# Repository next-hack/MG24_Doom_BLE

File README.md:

## MG24 Doom BLE
 Doom port to Silicon Labs' EFR32xG24 and MGM240x series microcontrollers and modules, with BLE multiplayer support.
 Coded by Nicola Wrachien.

The code is based on doomhack's GBA Doom Port (https://github.com/doomhack/GBADoom) with some Kippykip's additions, using the sources published on 2020. Thousands of changes have been made to fit to 256 kB of RAM, restore missing features, and enable multiplayer.

**Warning!** After you import the project on Simplicity Studio, you must "force project generation", so that the Gecko SDK files are copied on it. This is to comply with Silabs' licensing system. See "Building, developing, etc." below.

** News:**

**26/09/2024 Update! We have added support for The Gamepad, an open source gaming console based on the Arduino Nano Matter Board.
Please see https://next-hack.com/index.php/2024/09/21/the-gamepad-an-open-source-diy-handheld-gaming-console/ for more information about build information!
**

**12/03/2024 Update! Now peak 35 fps can be achieved also on 320 x 240 resolution thanks to partial screen refresh!**

**Features**

- Supports 320x200 and 320x240 resolution (the resolution can be changed at compile time)
- All the features of the original Doom are implemented:
  - full detail rendering, with Z-depth lighting.
  - 8-channel sound at 11025 Hz (samples with higher sample-rate are downsampled to 11025 Hz), mixed to 2 stereo channels.
  - Music with OPL2 emulation.
  - Monster behavior and sound propagation implemented.
  - Screen melt effect.
 - Extremely fast. Run almost always above 30 fps at 320x240, and even more at 320x200.
- Single player with save games and cheats support.
- Multiplayer features:
  - Each device can act as server or client.
  - Up to 4 players per game (server + 3 clients).
  - Game/player name can be edited using the menu.
  - Server can kick players in the lobby menu.
  - Clients can choose from up to 4 hosts.
  - Deathmatch or cooperative
  - Monster on/off.
  - Item respawn on/off
  - Time and frag limits.
  - Multiplayer over BLE.
  - Frame rate shown in the bottom-left corner (can be disabled with a compiler directive).
 - Additional features (with respect to vanilla Doom)
   - Player's weapon also is subjected to ambient light (as in PrBoom).
   - Background Doom title image becomes darker when Menus are turned on, to improve readability.
   - During networking games, kills messages are shown.
  - Tested with:
  - Shareware DOOM1.WAD.
  - Full Commercial DOOM.WAD
  - Partial Doom1.WAD v1.9 built-in demo support. Must be enabled by compiler directive.

**What's missing?**
- Only partial demo playback.
- Savegames do not store the whole status (might be implemented later), but only the current level and inventory.
- Need to be seriously debugged and cleaned up.

**Known issues**
- Multiplayer might be unstable in very crowded RF environments, i.e. joining might be difficult and 4-player game sometimes might be slow (from our tests, 3 player game is always fast, going at 30 fps).
- The display controller is driven via SPI and there is no with no vertical sync, so you can spot some artifacts due to sending new frame data, while the display is still refreshing the old frame.
- Only GSDK 4.3.2 is supported for now, with 10.2.1 GCC toolchain.

## Controls:
**Strafe:** alt + Left-Right
**Automap:** use + change weapon
**Menu:** alt + use
**Run** use + up-down

## Hardware:
In the "hardware" subdirectory you will find the project for the SparkFun Thing Plus Matter MGM240P board (SparkDoom subdir) and the WSTK adapter board .

## Content of this repository:
- MCUDoomWadUtil: source of the WAD converter (Code::Blocks project). Note that "mcudoom_0_4.wad" must be put in the same directory as the executable.
- DoomMG24BLE: the actual Doom port (Simplicity Studio 5.5 Project). **note!!!**: after you import the project with Simplicity Studio 5.5 project, you **must** "force generate" the project, so that the gecko sdk directory is recreated. This is because Silabs' GSDK has a different licensing, which requires you do download it from Simplicity Studio and accept the MSLA license.  Although you can download it from [Silicon Labs' github repo](https://github.com/SiliconLabs/gecko_sdk), using Simplicity Studio is strongly recommended, as only only the required files will be added.
- hardware: schematics.

## Building, developing, etc:
See https://next-hack.com/index.php/2023/12/10/multiplayer-doom-on-the-sparkfun-thing-plus-matter-board/
See also: https://next-hack.com/index.php/2024/09/21/the-gamepad-an-open-source-diy-handheld-gaming-console/

## License:
- Hardware: [Solderpad Hardware License version 2.1](https://solderpad.org/licenses/SHL-2.1)
- MCUDoomWadUtil: [GPLv2](https://www.gnu.org/licenses/old-licenses/gpl-2.0.en.html#SEC1)
- DoomMG24BLE
	- Original Doom code, modifications and its additions: GPLv2 or at your option later, as per original Doom/PrBoom sources.
	- [Marco Paland's printf](https://github.com/mpaland/printf): MIT License
	- Silicon Labs' GSDK (**note!** No GSDK files are provided due to its MSLA license, they must be downloaded from Simplicity Studio and restored to the project by forcing project generation): Silicon Lab's MSLA.
	- [Font8x8 By Daniel Hepper](https://github.com/dhepper/font8x8): Public Domain

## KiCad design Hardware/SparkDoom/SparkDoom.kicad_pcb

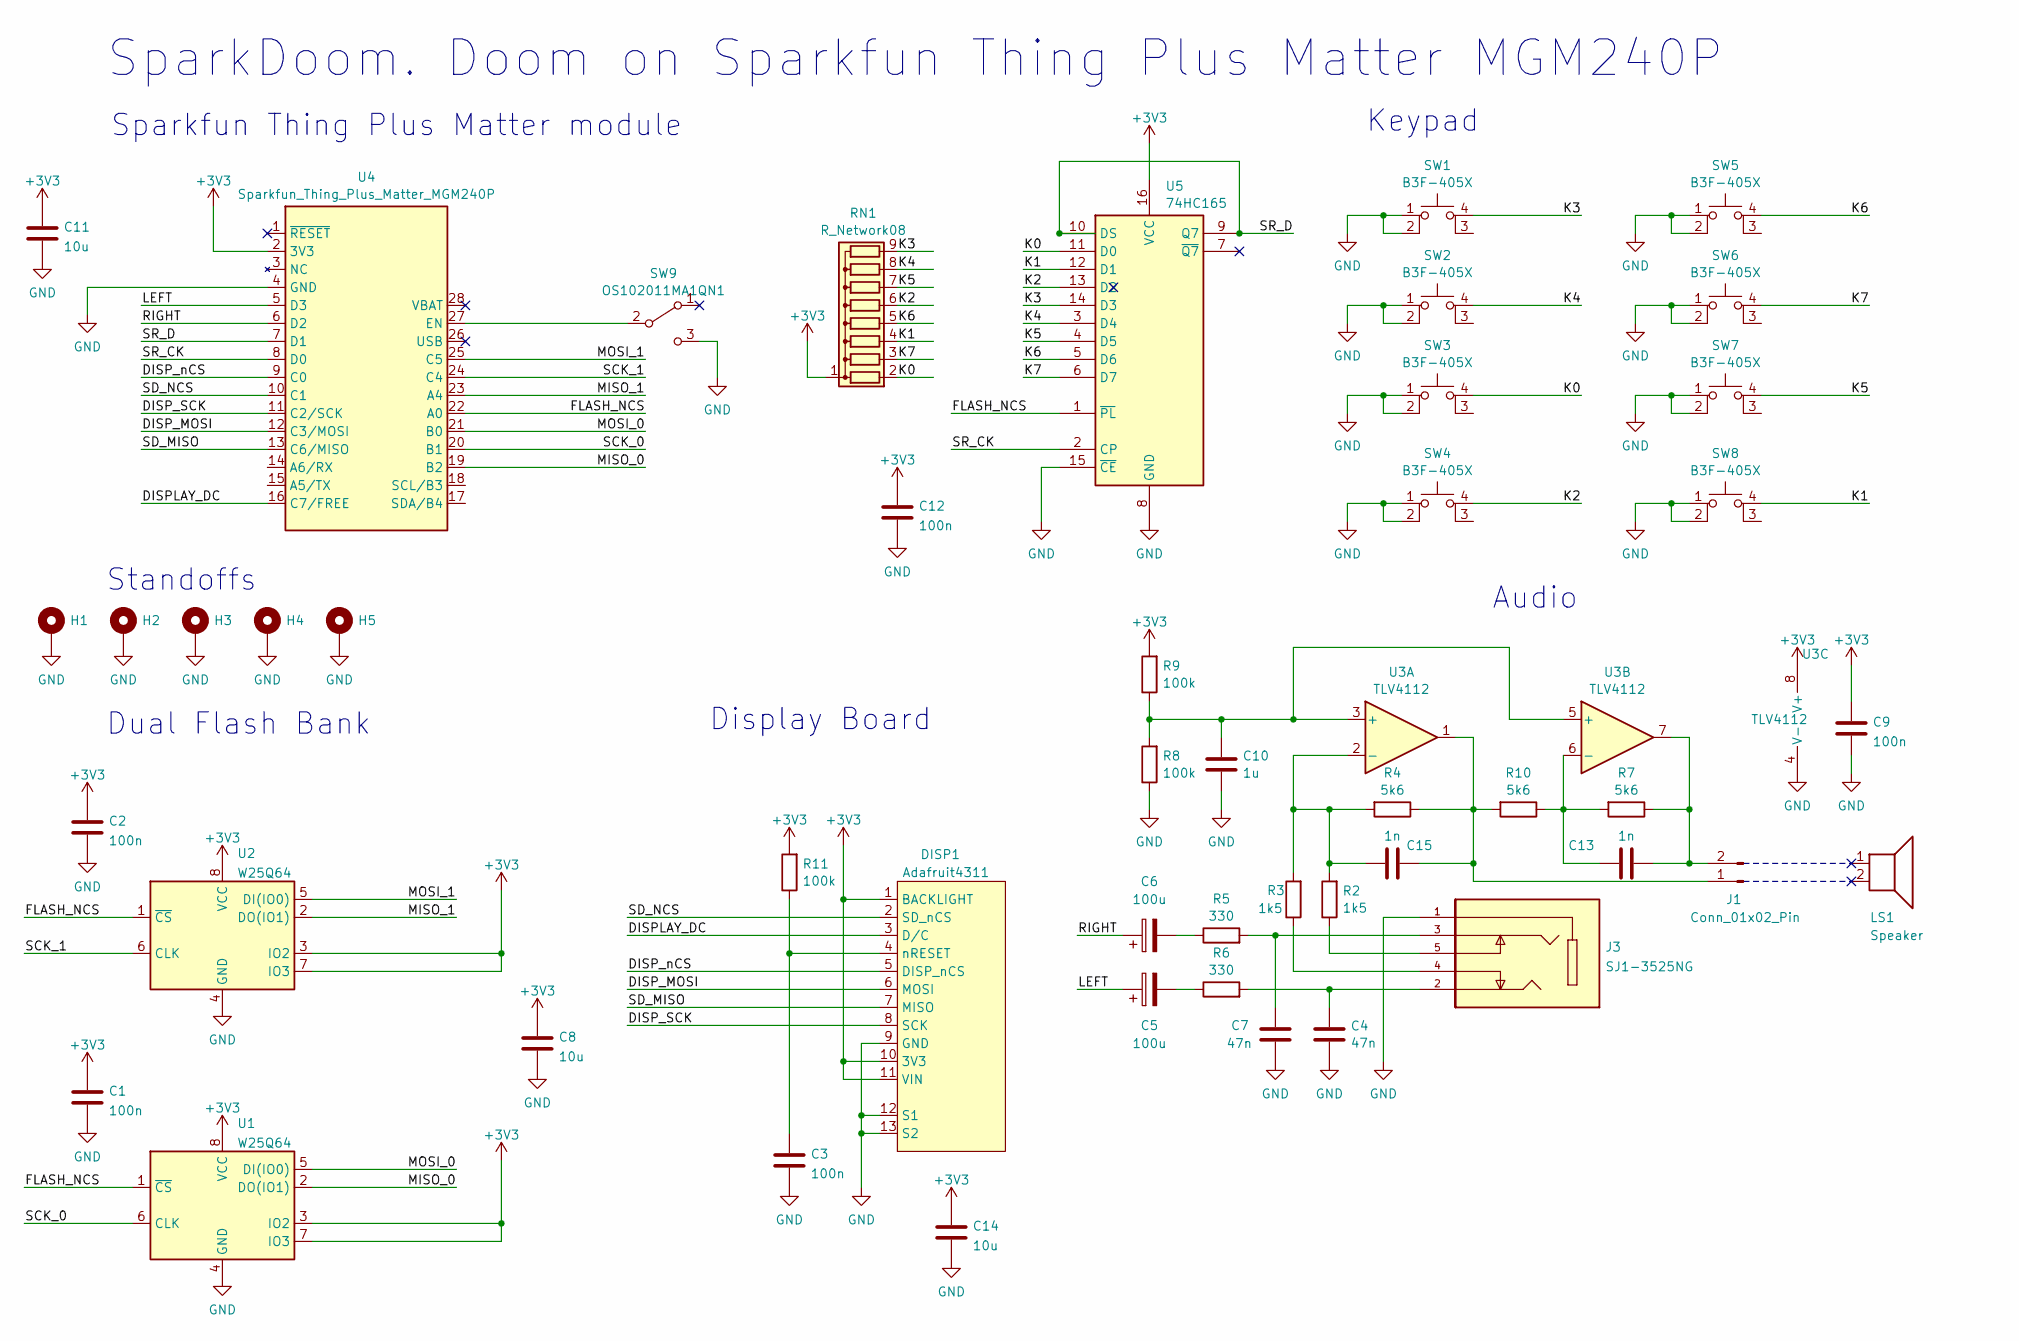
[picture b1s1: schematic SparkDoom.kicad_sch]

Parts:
C1, C2, C3, C9, C12: 100n; C_Disc_D3.8mm_W2.6mm_P2.50mm
C4, C7: 47n; C_Rect_L7.2mm_W2.5mm_P5.00mm_H6.5mm
C5, C6: 100u; CP_Radial_D6.3mm_P2.50mm
C8, C11, C14: 10u; C_Disc_D5.1mm_W3.2mm_P5.00mm
C10: 1u; C_Disc_D5.1mm_W3.2mm_P5.00mm
C13, C15: 1n; C_Disc_D3.8mm_W2.6mm_P2.50mm
DISP1: Adafruit4311
H1, H2, H3, H4, H5: MountingHole_Pad; MountingHole_2.7mm_M2.5_Pad
J1: Conn_01x02_Pin; PinHeader_1x02_P2.54mm_Horizontal
J3: SJ1-3525NG; CUI_SJ1-3525NG; PARTREV 1.01
LS1: Speaker; OWS-1330TA-8
R2, R3: 1k5; R_Axial_DIN0207_L6.3mm_D2.5mm_P10.16mm_Horizontal_ExactSilk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
R4, R7, R10: 5k6; R_Axial_DIN0207_L6.3mm_D2.5mm_P10.16mm_Horizontal_ExactSilk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
R5, R6: 330; R_Axial_DIN0207_L6.3mm_D2.5mm_P10.16mm_Horizontal_ExactSilk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
R8, R9, R11: 100k; R_Axial_DIN0207_L6.3mm_D2.5mm_P10.16mm_Horizontal_ExactSilk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
RN1: R_Network08; R_Array_SIP9
SW1, SW2, SW3, SW4, SW5, SW6, SW7, SW8: B3F-405X
SW9: OS102011MA1QN1
U1, U2: W25Q64; ADAFRUIT_QSPI8_DIP
U3: TLV4112; DIP-8_W7.62mm
U4: Sparkfun_Thing_Plus_Matter_MGM240P; SparkfunThingsPlusMatter
U5: 74HC165; DIP-16_W7.62mm

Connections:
+3V3: C1.1, C2.1, C8.1, C9.1, C11.1, C12.1, C14.1, DISP1.1 (BACKLIGHT), DISP1.10 (3V3), DISP1.11 (VIN), R9.2, R11.2, RN1.1 (common), U1.3 (IO2), U1.7 (IO3), U1.8 (VCC), U2.3 (IO2), U2.7 (IO3), U2.8 (VCC), U3.8 (V+), U4.2 (3V3), U5.16 (VCC)
/DISPLAY_DC: DISP1.3 (D/C), U4.16 (C7/FREE)
/DISP_MOSI: DISP1.6 (MOSI), U4.12 (C3/MOSI)
/DISP_SCK: DISP1.8 (SCK), U4.11 (C2/SCK)
/DISP_nCS: DISP1.5 (DISP_nCS), U4.9 (C0)
/FLASH_NCS: U1.1 (~CS), U2.1 (~CS), U4.22 (A0), U5.1 (~PL)
/K0: RN1.2 (R1), SW3.4 (A), U5.11 (D0)
/K1: RN1.4 (R3), SW8.4 (A), U5.12 (D1)
/K2: RN1.6 (R5), SW4.4 (A), U5.13 (D2)
/K3: RN1.9 (R8), SW1.4 (A), U5.14 (D3)
/K4: RN1.8 (R7), SW2.4 (A), U5.3 (D4)
/K5: RN1.7 (R6), SW7.4 (A), U5.4 (D5)
/K6: RN1.5 (R4), SW5.4 (A), U5.5 (D6)
/K7: RN1.3 (R2), SW6.4 (A), U5.6 (D7)
/LEFT: C5.1, U4.5 (D3)
/MISO_0: U1.2 (DO(IO1)), U4.19 (B2)
/MISO_1: U2.2 (DO(IO1)), U4.23 (A4)
/MOSI_0: U1.5 (DI(IO0)), U4.21 (B0)
/MOSI_1: U2.5 (DI(IO0)), U4.25 (C5)
/RIGHT: C6.1, U4.6 (D2)
/SCK_0: U1.6 (CLK), U4.20 (B1)
/SCK_1: U2.6 (CLK), U4.24 (C4)
/SD_MISO: DISP1.7 (MISO), U4.13 (C6/MISO)
/SD_NCS: DISP1.2 (SD_nCS), U4.10 (C1)
/SR_CK: U4.8 (D0), U5.2 (CP)
/SR_D: U4.7 (D1), U5.9 (Q7), U5.10 (DS)
GND: C1.2, C2.2, C3.2, C4.2, C7.2, C8.2, C9.2, C10.2, C11.2, C12.2, C14.2, DISP1.9 (GND), DISP1.12 (S1), DISP1.13 (S2), H1.1, H2.1, H3.1, H4.1, H5.1, J3.1, R8.1, SW1.1, SW1.2, SW2.1, SW2.2, SW3.1, SW3.2, SW4.1, SW4.2, SW5.1, SW5.2, SW6.1, SW6.2, SW7.1, SW7.2, SW8.1, SW8.2, SW9.3 (C), U1.4 (GND), U2.4 (GND), U3.4 (V-), U4.4 (GND), U5.8 (GND), U5.15 (~CE)
unnamed: C4.1, J3.2, R6.2
unnamed: C5.2, R6.1
unnamed: C6.2, R5.1
unnamed: C7.1, J3.3, R5.2
unnamed: C3.1, DISP1.4 (nRESET), R11.1
unnamed: C15.2, J1.1, R4.1, R10.2, U3.1
unnamed: C13.1, J1.2, R7.1, U3.7
unnamed: J3.4, R3.1
unnamed: J3.5, R2.1
unnamed: SW9.2 (B), U4.27 (EN)
unnamed: C10.1, R8.2, R9.1, U3.3 (+), U3.5 (+)
unnamed: C15.1, R2.2, R3.2, R4.2, U3.2 (-)
unnamed: C13.2, R7.2, R10.1, U3.6 (-)

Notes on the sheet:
Display Board
Sparkfun Thing Plus Matter module
Keypad
Dual Flash Bank
Audio
SparkDoom. Doom on Sparkfun Thing Plus Matter MGM240P
Standoffs

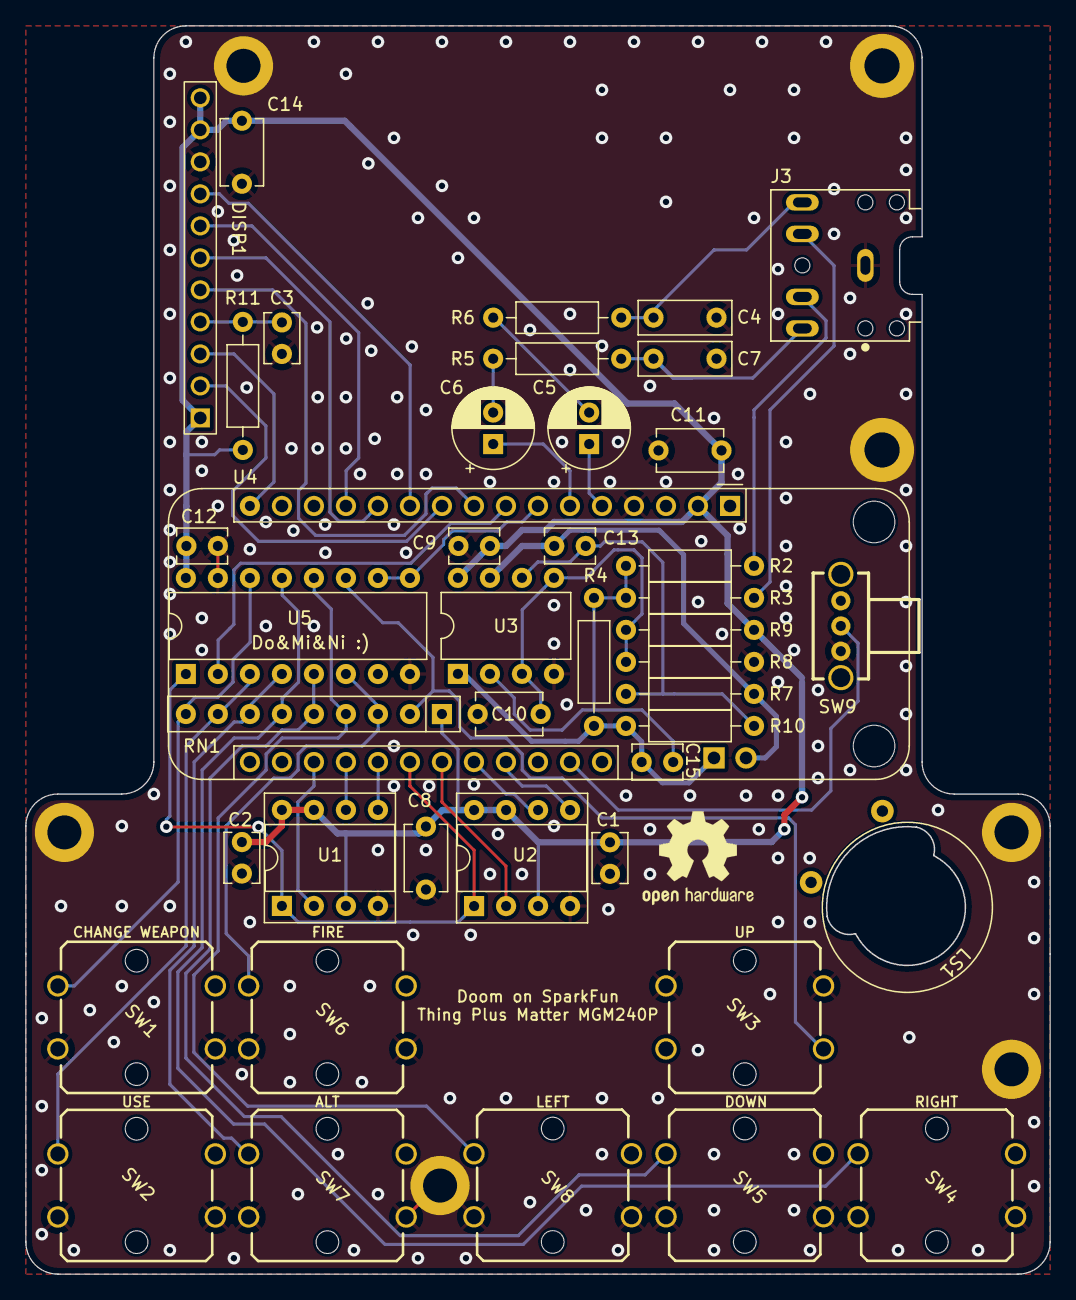
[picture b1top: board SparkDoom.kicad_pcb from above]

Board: 2 copper layers, 81.3 x 99.0 mm, 49 parts (1 on the bottom side), 40 nets.

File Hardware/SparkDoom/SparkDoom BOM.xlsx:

Ref des | Qty per Board | Value | Part Number
C1, C2, C3, C9, C12, | 5 | 100n | K104K10X7RF5TL2
C4, C7, | 2 | 47n | R82EC2470DQ60K
C5, C6, | 2 | 100u | ES5107M016AE1EA
C8, C11, C14, | 3 | 10u | FG28X5R1E106MRT06
C10, | 1 | 1u | FG28X7R1E105KRT06
C13, C15, | 2 | 1n | FG18C0G1H102JNT06
J1, | 1 | Conn_01x02_Pin | PH1RB-02-UA
J3, | 1 | SJ1-3525NG | CP1-3525NG-ND
LS1, | 1 | Speaker | 3949-OWS-1330TA-8-ND
R2, R3 | 2 | 1k5 | CF14JT1K5
R4, R7, R10, | 3 | 5k6 | CF14JT5K6
R8, R9, R11, | 3 | 100k | CF14JT100K
R5, R6, | 2 | 330R | CF14JT330R
RN1, | 1 | Network resistor | 4609X-101-153LF
SW1, SW2, SW3, SW4, SW5, SW6, SW7, SW8, | 8 | B3F-405X | B3F-4055
SW9, | 1 | OS102011MA1QN1 | OS102011MA1QN1
U1, U2, | 2 | W25Q64 breakout | 1528-5633-ND
U3, | 1 | TLV4112 | 296-10719-5-ND
U5, | 1 | 74HC165 | SN74HC165N
Wire for Speaker (each must be cut in half) | 0.5 | Wire | 1528-4934-ND
Screw Short | 5 | Screw short | 50M025045P006
Screw Long | 2 | Screw long | 50M025045P020
Spacers | 7 | Spacer | V6516A
Display Spacer | 2 | Spacer | R907-7
Button Caps White sq | 4 | Button | B32-1300
Button Caps Blue sq | 1 | Button Caps Blue sq | B32-1340
Button Caps Yellow sq | 1 | Button Caps Yellow sq | B32-1330
Button Caps Light Green | 1 | Button Caps Light Green | B32-1370
Button Caps Orange | 1 | Button Caps Orange | B32-1320
Connectors for SF board Male 12 Pin | 1 | Connectors for SF board Male 12 Pin | PH1-12-UA
Connectors for SF board Female 12 Pin | 1 | Connectors for SF board Female 12 Pin | PPTC121LFBN-RC
Connectors for SF board Male 16 Pin | 1 | Connectors for SF board Male 16 Pin | PH1-16-UA
Connectors for SF board Female 16 Pin | 1 | Connectors for SF board Female 16 Pin | PPTC161LFBN-RC
Display | 1 | Display 320x240 | Adafruit 4311
Connector for Display (Female 11 Pin) | 1 | Connector for Display (Female 11 Pin) | PPTC111LFBN-RC
Socket 16 pin | 1 | Socket 16 pin | ICS-316-T
Socket 8 pin | 3 | Socket 8 pin | ICS-308-T
Sparkfun ThingsPlus Matter | 1 | Sparkfun ThingsPlus Matter | 1568-DEV-20270-ND
Battery | 1 | https://www.sparkfun.com/products/13851 | See link in description

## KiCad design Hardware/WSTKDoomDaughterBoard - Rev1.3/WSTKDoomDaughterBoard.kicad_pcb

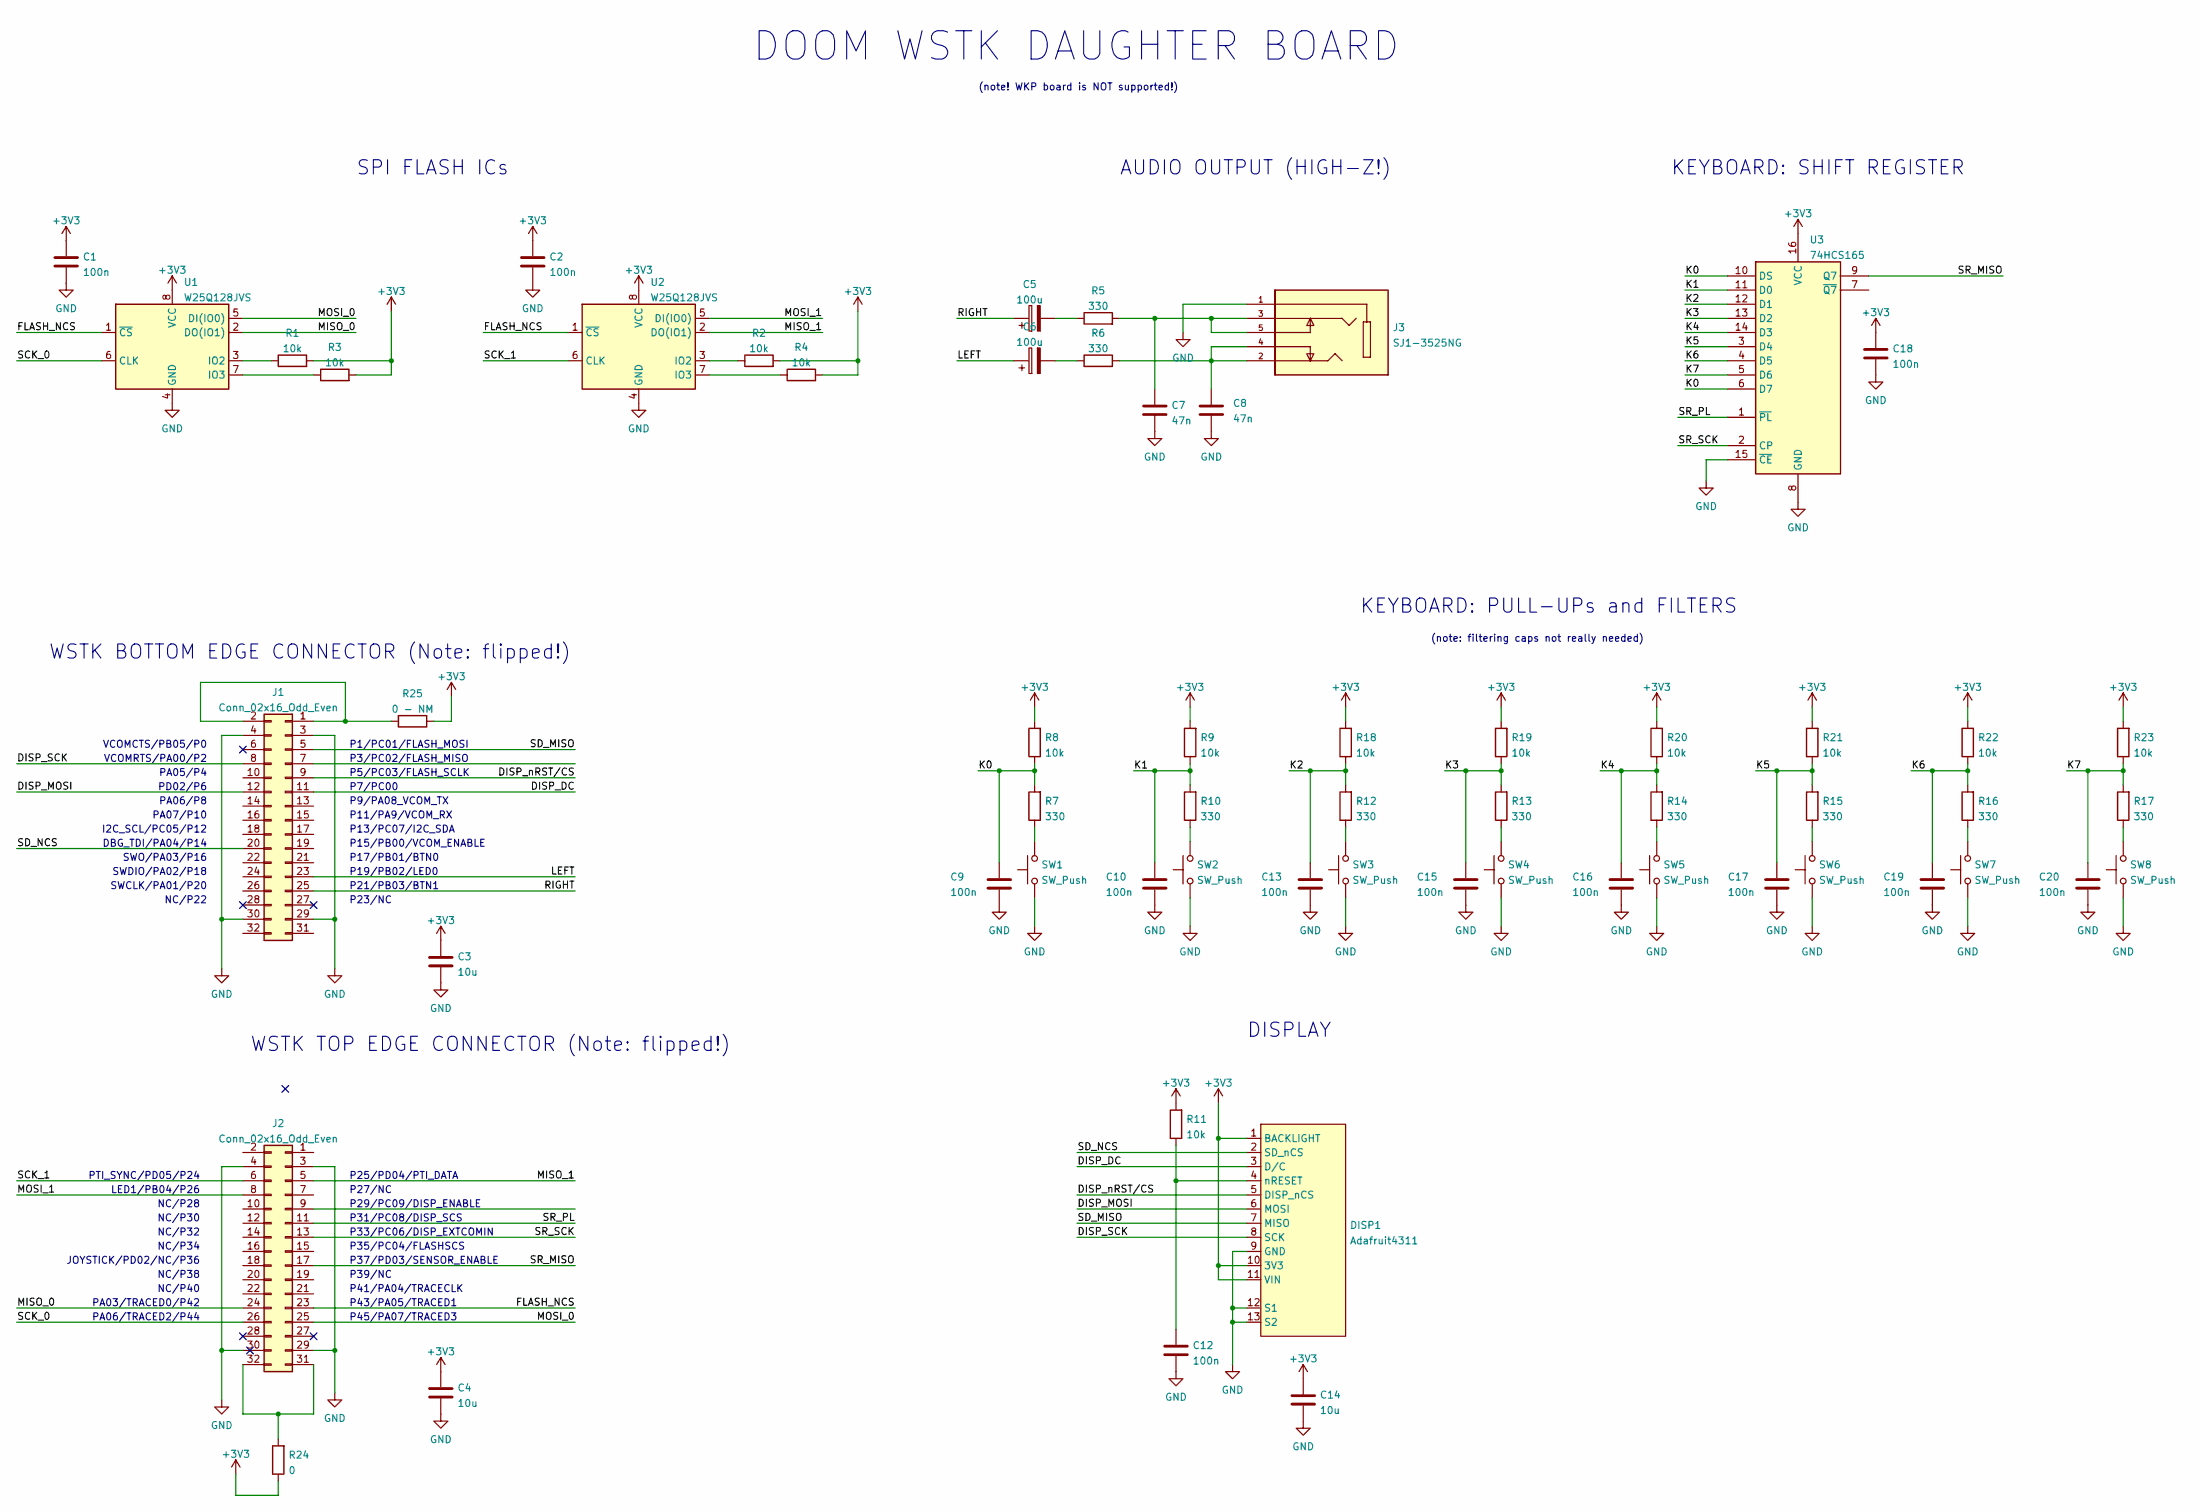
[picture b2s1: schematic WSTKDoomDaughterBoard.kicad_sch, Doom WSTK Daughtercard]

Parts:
C1, C2, C9, C10, C12, C13, C15, C16, C17, C18, C19, C20: 100n; C_0603_1608Metric
C3, C4, C14: 10u; C_0603_1608Metric
C5, C6: 100u; CP_Radial_D6.3mm_P2.50mm
C7, C8: 47n; C_0603_1608Metric
DISP1: Adafruit4311
J1, J2: Conn_02x16_Odd_Even; PinHeader_2x16_P2.54mm_Vertical
J3: SJ1-3525NG; CUI_SJ1-3525NG; PARTREV 1.01
R1, R2, R3, R4, R8, R9, R11, R18, R19, R20, R21, R22, R23: 10k; R_0603_1608Metric
R5, R6, R7, R10, R12, R13, R14, R15, R16, R17: 330; R_0603_1608Metric
R24: 0; R_0603_1608Metric
R25: 0 - NM; R_0603_1608Metric
SW1, SW2, SW3, SW4, SW5, SW6, SW7, SW8: SW_Push; SW_PUSH_6mm
U1, U2: W25Q128JVS; SOIC-8_5.275x5.275mm_P1.27mm
U3: 74HCS165; SOIC-16_3.9x9.9mm_P1.27mm

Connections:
+3V3: C1.1, C2.1, C3.1, C4.1, C14.1, C18.1, DISP1.1 (BACKLIGHT), DISP1.10 (3V3), DISP1.11 (VIN), R1.2, R2.2, R3.2, R4.2, R8.2, R9.2, R11.2, R18.2, R19.2, R20.2, R21.2, R22.2, R23.2, R24.1, R25.1, U1.8 (VCC), U2.8 (VCC), U3.16 (VCC)
/DISP_DC: DISP1.3 (D/C), J1.11
/DISP_MOSI: DISP1.6 (MOSI), J1.12
/DISP_SCK: DISP1.8 (SCK), J1.8
/DISP_nRST/CS: DISP1.5 (DISP_nCS), J1.9
/FLASH_NCS: J2.23, U1.1 (~CS), U2.1 (~CS)
/K0: C9.1, R7.2, R8.1, U3.6 (D7), U3.10 (DS)
/K1: C10.1, R9.1, R10.2, U3.11 (D0)
/K2: C13.1, R12.2, R18.1, U3.12 (D1)
/K3: C15.1, R13.2, R19.1, U3.13 (D2)
/K4: C16.1, R14.2, R20.1, U3.14 (D3)
/K5: C17.1, R15.2, R21.1, U3.3 (D4)
/K6: C19.1, R16.2, R22.1, U3.4 (D5)
/K7: C20.1, R17.2, R23.1, U3.5 (D6)
/LEFT: C6.1, J1.23
/MISO_0: J2.24, U1.2 (DO(IO1))
/MISO_1: J2.5, U2.2 (DO(IO1))
/MOSI_0: J2.25, U1.5 (DI(IO0))
/MOSI_1: J2.8, U2.5 (DI(IO0))
/RIGHT: C5.1, J1.25
/SCK_0: J2.26, U1.6 (CLK)
/SCK_1: J2.6, U2.6 (CLK)
/SD_MISO: DISP1.7 (MISO), J1.5
/SD_NCS: DISP1.2 (SD_nCS), J1.20
/SR_MISO: J2.17, U3.9 (Q7)
/SR_PL: J2.11, U3.1 (~PL)
/SR_SCK: J2.13, U3.2 (CP)
GND: C1.2, C2.2, C3.2, C4.2, C7.2, C8.2, C9.2, C10.2, C12.2, C13.2, C14.2, C15.2, C16.2, C17.2, C18.2, C19.2, C20.2, DISP1.9 (GND), DISP1.12 (S1), DISP1.13 (S2), J1.3, J1.4, J1.29, J1.30, J2.3, J2.4, J2.29, J2.30, J3.1, SW1.1, SW2.1, SW3.1, SW4.1, SW5.1, SW6.1, SW7.1, SW8.1, U1.4 (GND), U2.4 (GND), U3.8 (GND), U3.15 (~CE)
unnamed: C5.2, R5.1
unnamed: C6.2, R6.1
unnamed: C7.1, J3.3, J3.5, R5.2
unnamed: C8.1, J3.2, J3.4, R6.2
unnamed: C12.1, DISP1.4 (nRESET), R11.1
unnamed: J1.1, J1.2, R25.2
unnamed: J2.31, J2.32, R24.2
unnamed: R1.1, U1.3 (IO2)
unnamed: R2.1, U2.3 (IO2)
unnamed: R3.1, U1.7 (IO3)
unnamed: R4.1, U2.7 (IO3)
unnamed: R7.1, SW1.2
unnamed: R10.1, SW2.2
unnamed: R12.1, SW3.2
unnamed: R13.1, SW4.2
unnamed: R14.1, SW5.2
unnamed: R15.1, SW6.2
unnamed: R16.1, SW7.2
unnamed: R17.1, SW8.2

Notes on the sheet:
PA06/TRACED2/P44
KEYBOARD: SHIFT REGISTER
LED1/PB04/P26
P21/PB03/BTN1
P3/PC02/FLASH_MISO
JOYSTICK/PD02/NC/P36
SWDIO/PA02/P18
DBG_TDI/PA04/P14
PA06/P8
P31/PC08/DISP_SCS
WSTK BOTTOM EDGE CONNECTOR (Note: flipped!)
(note: filtering caps not really needed)
NC/P40
P41/PA04/TRACECLK
P7/PC00
NC/P28
P11/PA9/VCOM_RX
(note! WKP board is NOT supported!)
KEYBOARD: PULL-UPs and FILTERS
P13/PC07/I2C_SDA
NC/P22
P17/PB01/BTN0
P1/PC01/FLASH_MOSI
SWO/PA03/P16
P25/PD04/PTI_DATA
P33/PC06/DISP_EXTCOMIN
NC/P32
P27/NC
P23/NC
DOOM WSTK DAUGHTER BOARD
PTI_SYNC/PD05/P24
WSTK TOP EDGE CONNECTOR (Note: flipped!)
P45/PA07/TRACED3
PD02/P6
P29/PC09/DISP_ENABLE
P35/PC04/FLASHSCS
PA07/P10
P39/NC
SPI FLASH ICs
P19/PB02/LED0

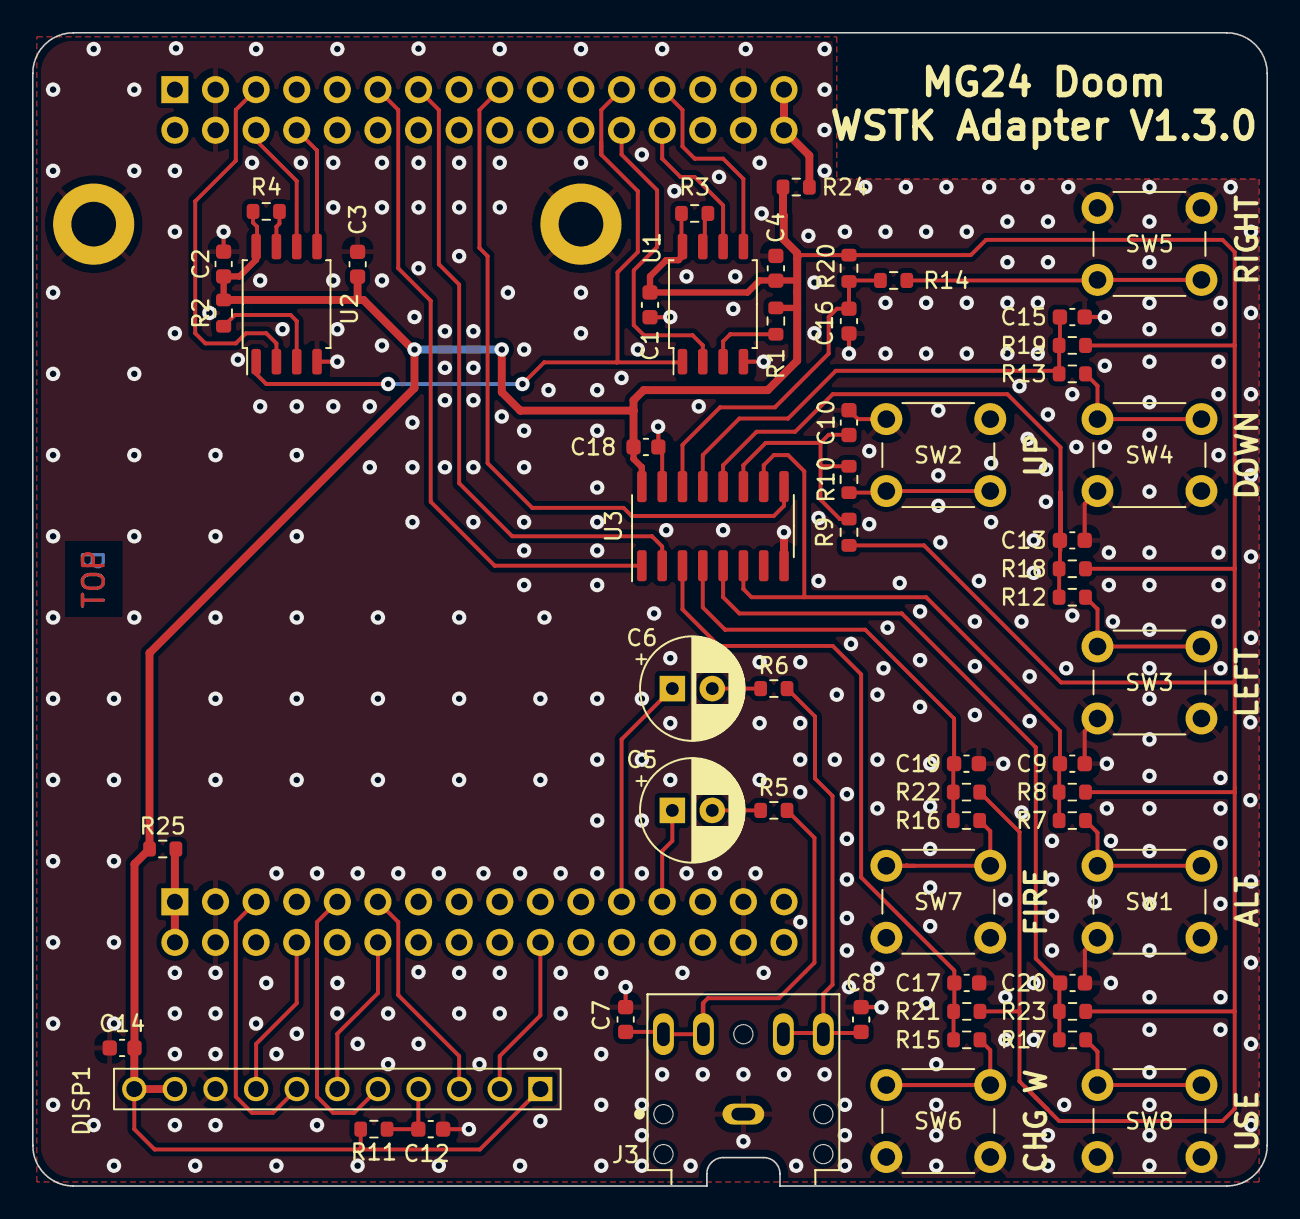
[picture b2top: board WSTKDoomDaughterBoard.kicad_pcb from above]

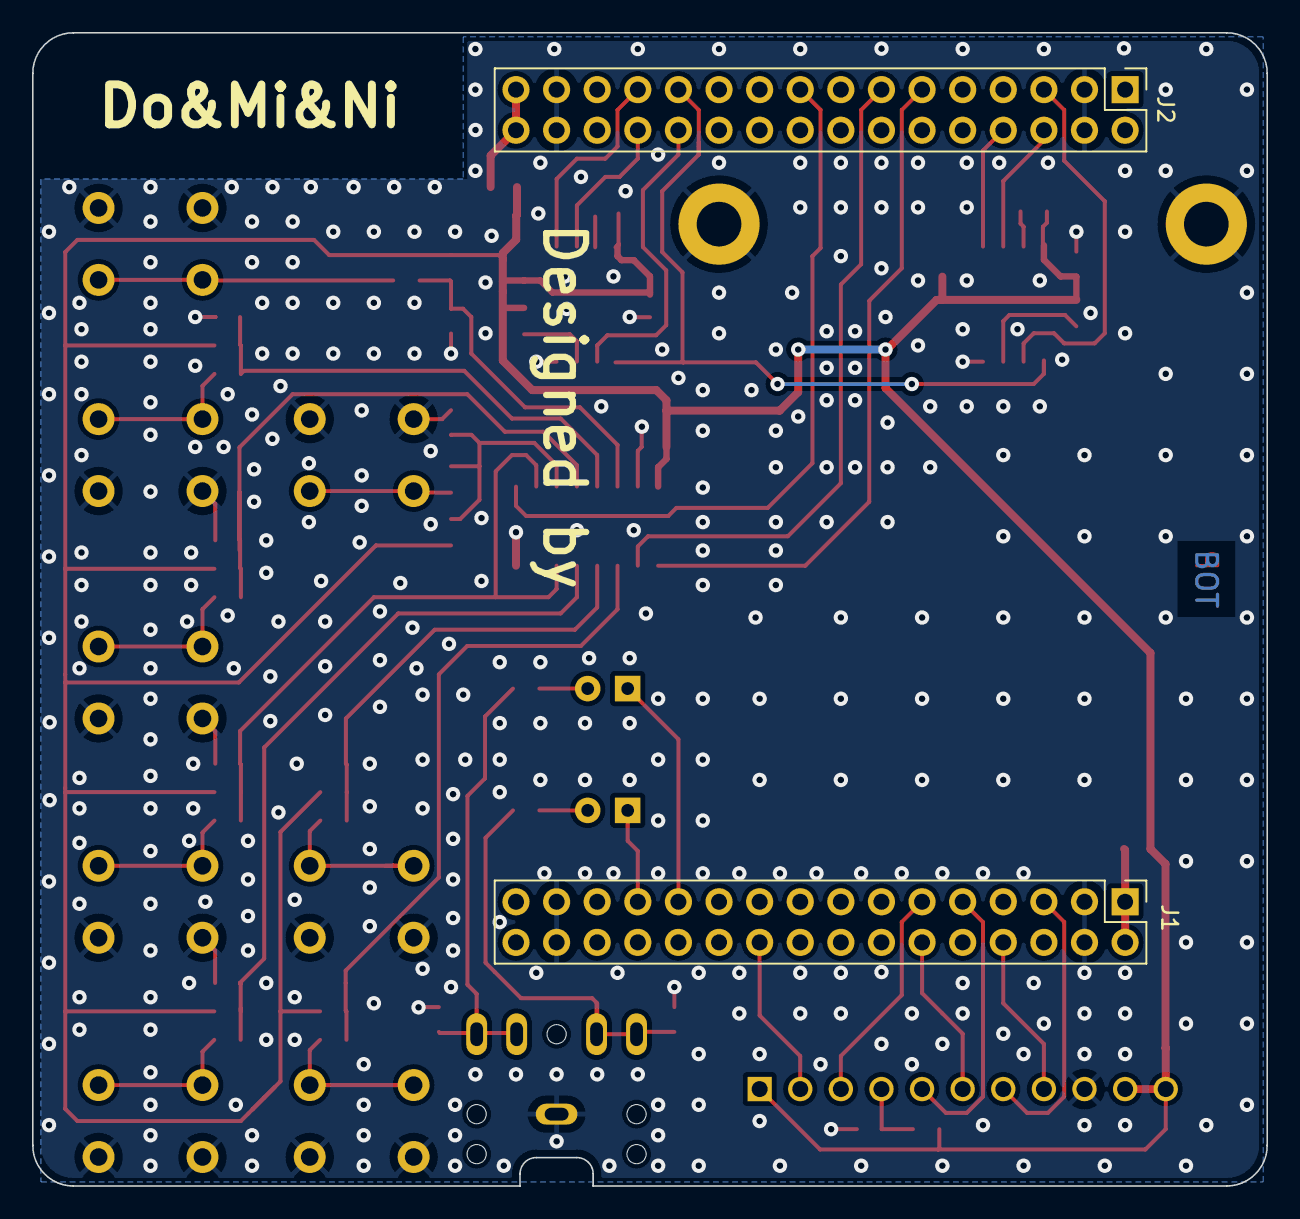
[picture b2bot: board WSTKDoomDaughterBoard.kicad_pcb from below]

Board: 2 copper layers, 77.2 x 72.1 mm, 59 parts (2 on the bottom side), 47 nets.

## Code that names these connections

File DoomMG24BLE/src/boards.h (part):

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  #define SECOND_FLASH_SPI_MISO_PIN             2
  #define SECOND_FLASH_SPI_CLK_PIN              9
  // common chip select for both flash
  #define FLASH_NCS_PORT                        gpioPortA
  #define FLASH_NCS_PIN                         6
  //
  // display config
  //
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  //
  #define DISPLAY_USES_RESET_INSTEAD_OF_NCS     1 // for displays without CS...
  //
  #define DISPLAY_DC_PORT                       gpioPortD
  #define DISPLAY_DC_PIN                        5
  //
  #define DISPLAY_RES_PORT                      gpioPortC
  #define DISPLAY_RES_PIN                       1
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  #define KEY_LEFT                              0x02
  #define KEY_RIGHT                             0x08
  //
  #define SR_MISO_PORT                          gpioPortD
  #define SR_MISO_PIN                           3
  //
  #define SR_CLK_PORT                           gpioPortC
  #define SR_CLK_PIN                            6
  //
  #define SR_PL_PORT                            gpioPortC
  #define SR_PL_PIN                             8
  //
  // SD related stuff
  #define HAS_SD                                1
  #define SD_NCS_PORT                           gpioPortC
  #define SD_NCS_PIN                            1
  #define SD_MISO_PORT                          gpioPortC
  #define SD_MISO_PIN                           3


  // Not used i2c stuff
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  #define SECOND_FLASH_SPI_MISO_PIN             4
  #define SECOND_FLASH_SPI_CLK_PIN              5
  // common chip select for both flash
  #define FLASH_NCS_PORT                        gpioPortA
  #define FLASH_NCS_PIN                         5
  //
  // display config
  //
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  //
  #define DISPLAY_USES_RESET_INSTEAD_OF_NCS     0 // for displays without CS...
  //
  #define DISPLAY_DC_PORT                       gpioPortA
  #define DISPLAY_DC_PIN                        0
  //
  #define DISPLAY_RES_PORT                      // not used
  #define DISPLAY_RES_PIN                       // not used
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  #define KEY_LEFT                              0x02
  #define KEY_RIGHT                             0x08
  //
  #define SR_MISO_PORT                          gpioPortD
  #define SR_MISO_PIN                           3
  //
  #define SR_CLK_PORT                           gpioPortC
  #define SR_CLK_PIN                            6
  //
  #define SR_PL_PORT                            gpioPortC
  #define SR_PL_PIN                             8

  // SD related stuff
  #define HAS_SD                                1
  #define SD_NCS_PORT                           gpioPortA
  #define SD_NCS_PIN                            4
  #define SD_MISO_PORT                          gpioPortC
  #define SD_MISO_PIN                           1
  // Not used i2c stuff
  // #define I2C_SCL_PIN_NUMBER                    // not used
  // #define I2C_SCL_PORT_NUMBER                   // not used
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  #define SECOND_FLASH_SPI_MISO_PIN             4
  #define SECOND_FLASH_SPI_CLK_PIN              5
  // common chip select for both flash
  #define FLASH_NCS_PORT                        gpioPortA
  #define FLASH_NCS_PIN                         5
  //
  // display config
  //
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  //
  #define DISPLAY_USES_RESET_INSTEAD_OF_NCS     0 // for displays without CS...
  //
  #define DISPLAY_DC_PORT                       gpioPortC//gpioPortA
  #define DISPLAY_DC_PIN                        0
  //
  #define DISPLAY_RES_PORT                      // not used
  #define DISPLAY_RES_PIN                       // not used
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  #define KEY_LEFT                              0x02
  #define KEY_RIGHT                             0x04
  //
  #define SR_MISO_PORT                          gpioPortD
  #define SR_MISO_PIN                           1
  //
  #define SR_CLK_PORT                           gpioPortD
  #define SR_CLK_PIN                            0
  //
  #define SR_PL_PORT                            gpioPortA
  #define SR_PL_PIN                             0

  // SD related stuff
  #define HAS_SD                                1
  #define SD_NCS_PORT                           gpioPortC
  #define SD_NCS_PIN                            1
  #define SD_MISO_PORT                          gpioPortC
  #define SD_MISO_PIN                           6
  // Not used i2c stuff
  // #define I2C_SCL_PIN_NUMBER                    // not used
  // #define I2C_SCL_PORT_NUMBER                   // not used
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  #define SECOND_FLASH_SPI_MISO_PIN             4
  #define SECOND_FLASH_SPI_CLK_PIN              4
  // common chip select for both flash
  #define FLASH_NCS_PORT                        gpioPortA
  #define FLASH_NCS_PIN                         0
  //
  // display config
  //
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  //
  #define DISPLAY_USES_RESET_INSTEAD_OF_NCS     0 // for displays without CS...
  //
  #define DISPLAY_DC_PORT                       gpioPortC
  #define DISPLAY_DC_PIN                        7
  //
  #define DISPLAY_RES_PORT                      // not used
  #define DISPLAY_RES_PIN                       // not used
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  #define KEY_LEFT                              0x02
  #define KEY_RIGHT                             0x04
  //
  #define SR_MISO_PORT                          gpioPortA
  #define SR_MISO_PIN                           3
  //
  #define SR_CLK_PORT                           gpioPortC
  #define SR_CLK_PIN                            6
  //
  #define SR_PL_PORT                            gpioPortC
  #define SR_PL_PIN                             0

  // SD related stuff
  #define HAS_SD                                1
  #define SD_NCS_PORT                           gpioPortC
  #define SD_NCS_PIN                            8
  #define SD_MISO_PORT                          gpioPortD
  #define SD_MISO_PIN                           3
  // Not used i2c stuff
  // #define I2C_SCL_PIN_NUMBER                    // not used
  // #define I2C_SCL_PORT_NUMBER                   // not used
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  #define SECOND_FLASH_SPI_MISO_PIN             6
  #define SECOND_FLASH_SPI_CLK_PIN              7
  // common chip select for both flash
  #define FLASH_NCS_PORT                        gpioPortC
  #define FLASH_NCS_PIN                         0
  //
  // display config
  //
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  //
  #define DISPLAY_USES_RESET_INSTEAD_OF_NCS     0 // for displays without CS...
  //
  #define DISPLAY_DC_PORT                       gpioPortA  //ok
  #define DISPLAY_DC_PIN                        9          //ok
  //
  #define DISPLAY_RES_PORT                      // not used
  #define DISPLAY_RES_PIN                       // not used
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  #define JOYPAD_LEFT_Y_PORT                    gpioPortC
  #define JOYPAD_LEFT_Y_PIN                     9
    //
  #define SR_MISO_PORT                          gpioPortA
  #define SR_MISO_PIN                           5
  //
  #define SR_CLK_PORT                           gpioPortA
  #define SR_CLK_PIN                            4
  //
  #define SR_PL_PORT                            gpioPortD
  #define SR_PL_PIN                             5

  // SD related stuff
  #define HAS_SD                                1
  #define SD_NCS_PORT                           gpioPortB
  #define SD_NCS_PIN                            2
  #define SD_MISO_PORT                          gpioPortC
  #define SD_MISO_PIN                           0
  // Not used i2c stuff
  // #define I2C_SCL_PIN_NUMBER                    // not used
  // #define I2C_SCL_PORT_NUMBER                   // not used
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  #define SECOND_FLASH_SPI_MISO_PIN             4
  #define SECOND_FLASH_SPI_CLK_PIN              3
  // common chip select for both flash
  #define FLASH_NCS_PORT                        gpioPortD
  #define FLASH_NCS_PIN                         5
  //
  // display config
  //
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  //
  #define DISPLAY_USES_RESET_INSTEAD_OF_NCS     0 // for displays without CS...
  //
  #define DISPLAY_DC_PORT                       gpioPortC
  #define DISPLAY_DC_PIN                        7
  //
  #define DISPLAY_RES_PORT                      // not used
  #define DISPLAY_RES_PIN                       // not used
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#error unsupported board
#endif
// common hardware-related macros and defines
#define FLASH_NCS_LOW()                   GPIO->P_CLR[FLASH_NCS_PORT].DOUT = (1 << FLASH_NCS_PIN)
#define FLASH_NCS_HIGH()                  GPIO->P_SET[FLASH_NCS_PORT].DOUT = (1 << FLASH_NCS_PIN)
//
#ifdef __cplusplus
}
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
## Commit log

2023-12-11 Hardware, MCUWadUtil and Doom Port.
2023-12-19 Changed timings for improved connectivity
2023-12-19 Fixed bad animated flat when switching between networked and regular game. Improved a lot network join stability.
    - switching from networked and single player will change level data due to different amount of items.
    - We are now not processing just a single stack message when we are in menu mode.
2023-12-19 Added BLE message processing while waiting display DMA to finish.
2024-01-10 Fix initial hardfault because trying to access BLE functions when BLE is not initialized yet.
    Notes:
    1) With old code, eventually (By chance!) it would recover.
    2) Need cleanup.
2024-03-12 Fixed no sound output for doors/etc.
2024-03-12 Added partial screen refresh so that 35fps (peak) can be achieved also on 320 x 240 resolution!
2024-08-17 Slot hole for battery wires.
2024-08-18 Fix bug for SPI flash, entering a deadlock. Fixed a couple of typos.
2024-10-01 Added support for The Gamepad

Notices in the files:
DoomMG24BLE/src/boards.h:
Copyright (C) 2022-2023 by Nicola Wrachien
modify it under the terms of the GNU General Public License
